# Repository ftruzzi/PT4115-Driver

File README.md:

PT4115 3-channel LED driver
===========================

Eagle files for my PT4115 3-channel (RGB) LED driver.

<p align="center">
  
</p>

##Features and parts list:

* **C1, C2, C3**: 22uF tantalum capacitors (DigiKey part number: 399-3781-1-ND)
* **D1, D2, D3**; Schottky diode 2A SMA package  (DigiKey part number: B240A-FDICT-ND)
* **L1, L2, L3**: 68uH power inductor, 0.7A (DigiKey part number: PCD2117CT-ND)
* **R1, R2, R3**: 0.33ohm resistors, 0805 package. These are current sense resistors. Current I=0.1/R (at maximum brightness).
* **4x screw terminals**: 3.5mm (bought mine on Tayda Electronics)
* **3x PT4115 drivers** (you can find them dirt cheap on eBay or Aliexpress)
* **1x 4-pin + 1x 2-pin** male or female headers.

Feel free to visit my website at http://truzzi.me.

Suggestions and feedback are very welcome!

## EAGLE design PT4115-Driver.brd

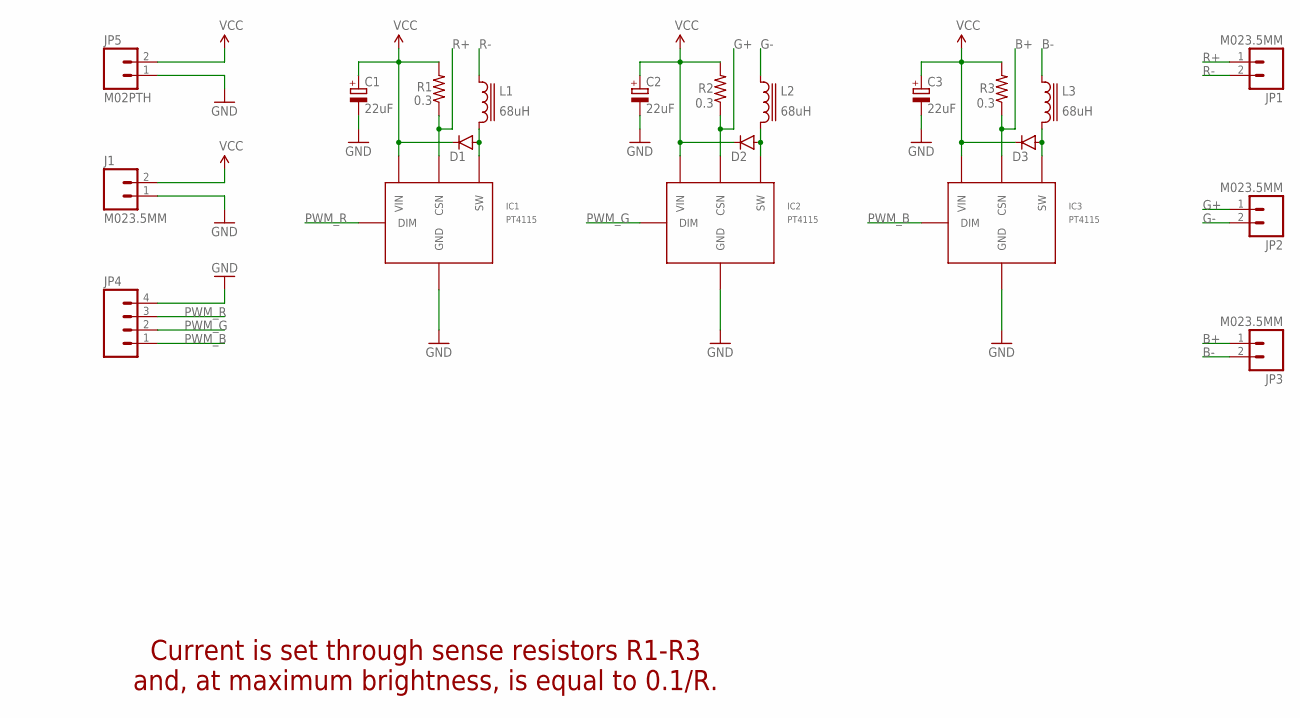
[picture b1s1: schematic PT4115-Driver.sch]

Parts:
C1, C2, C3: 22uF; D/7343-31R
D1, D2, D3: DIODESMA-KIT; SMA-DIODE-KIT
IC1, IC2, IC3: PT4115
J1: M023.5MM; SCREWTERMINAL-3.5MM-2
JP1, JP2, JP3: M023.5MM; SCREWTERMINAL-3.5MM-2
JP4: M04LONGPADS; 1X04_LONGPADS
JP5: M02PTH; 1X02
L1, L2, L3: 68uH; ELL6
R1, R2, R3: 0.3; 0805

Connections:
B+: IC3.4 (CSN), JP3.1, R3.1
B-: JP3.2, L3.1
G+: IC2.4 (CSN), JP2.1, R2.1
G-: JP2.2, L2.1
GND: C1.-, C2.-, C3.-, IC1.2 (GND), IC1.2A (GND), IC2.2 (GND), IC2.2A (GND), IC3.2 (GND), IC3.2A (GND), J1.1, JP4.4, JP5.1
unnamed: D1.A, IC1.1 (SW), L1.2
unnamed: D2.A, IC2.1 (SW), L2.2
unnamed: D3.A, IC3.1 (SW), L3.2
PWM_B: IC3.3 (DIM), JP4.1
PWM_G: IC2.3 (DIM), JP4.2
PWM_R: IC1.3 (DIM), JP4.3
R+: IC1.4 (CSN), JP1.1, R1.1
R-: JP1.2, L1.1
VCC: C1.+, C2.+, C3.+, D1.C, D2.C, D3.C, IC1.5 (VIN), IC2.5 (VIN), IC3.5 (VIN), J1.2, JP5.2, R1.2, R2.2, R3.2

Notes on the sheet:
Current is set through sense resistors R1-R3 and, at maximum brightness, is equal to 0.1/R.

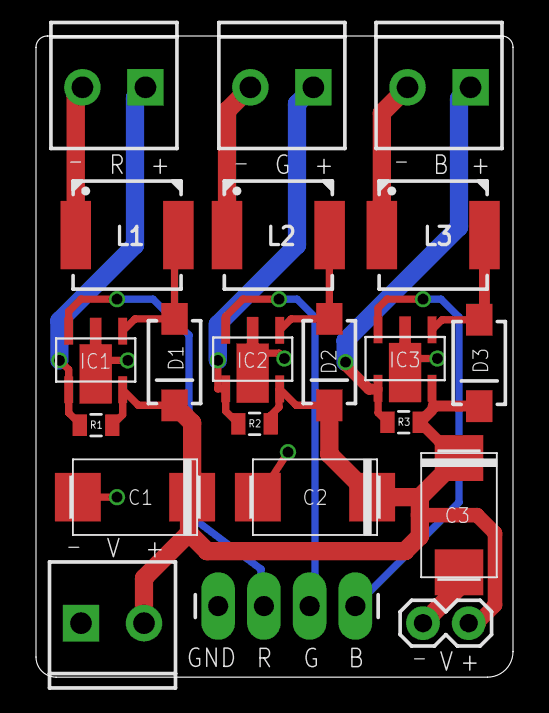
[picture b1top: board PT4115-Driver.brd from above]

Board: 2 copper layers, 26.5 x 35.6 mm, 21 parts (0 on the bottom side), 14 nets.

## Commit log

2015-01-29 :neckbeard: Added .gitattributes
2015-01-29 Eagle files for my PT4115 3-channel LED driver.
2015-01-30 Improved schematics and board aesthetics
2015-01-30 Fixed parts' values
2015-01-30 Added image

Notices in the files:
PT4115-Driver.sch:
LICENSE: Released under CC BY-NC-SA 4.0
parts and their libraries:
SparkFun-Connectors: Licensing: Creative Commons ShareAlike 4.0 International - https://creativecommons.org/licenses/by-sa/4.0
inductor-panasonic: Copyright (C) 2009, Bob Starr
